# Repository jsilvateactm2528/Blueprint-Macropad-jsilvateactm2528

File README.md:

# Blueprint-Macropad-jsilvateactm2528
João Macropad is a 7 key macropad with 2 rotary encoders, an OLED Display. It also has 7 SK6812 MINI-E LEDs, and uses QMK firmware 

I spend a lot of hours on this build (I forgot to keep track of the time), because I'm new in this area and this is my first project. 

João Macropad is a compact macropad featuring 7 mechanical keys, 2 rotary encoders, a OLED display, and 7 rgb leds. 

It was designed as a personal open-source hardware project.

## Features

* 7 mechanical keys (For macros)
* 2 EC11 rotary encoder with push button (One change volume and mute and the other rotate to move up and down a list of options on the OLED screen and press to select one of the options.)
* 4 pin 128x32 OLED display (At the moment, I don´t know for sure what options I will have in the display.)
* 7 SK6812 MINI-E LEDs (Just to illuminate the macropad.)
* Seeed Studio XIAO microcontroller
* QMK firmware

## PCB

I used Kicad and it's a great program

* Shematics
* Pcb
* 3d view of the top and botom part of the pcb

## Case

The case was designed to be compact, simple, and functional, with easy access to all components from the top.

## Firmware

I used QMK for all of it

* One of the rotary encoder changes volume, press to mute and the other move up and down a list of options on the OLED screen and press to select one of the options.
* The 4 keys currently act as macros.
* The OLED will have a list of shortcuts (plan on ading the list via a windows app)
* The LEDs are normally changing between red, blue, green, and yellow.

## BOM

* 7x MX-Style switches
* 7x Keycaps
* 4x M3x5x4 Heatset inserts
* 4x M3x16mm screws
* 9x 1N4148 Diodes.
* 7x SK6812 MINI-E LEDs
* 1x 0.91" 128x32 OLED Display
* 2x EC11 Rotary Encoder
* 1x XIAO RP2040
* 1x Case (2 printed parts)
* 1x Custom pcb

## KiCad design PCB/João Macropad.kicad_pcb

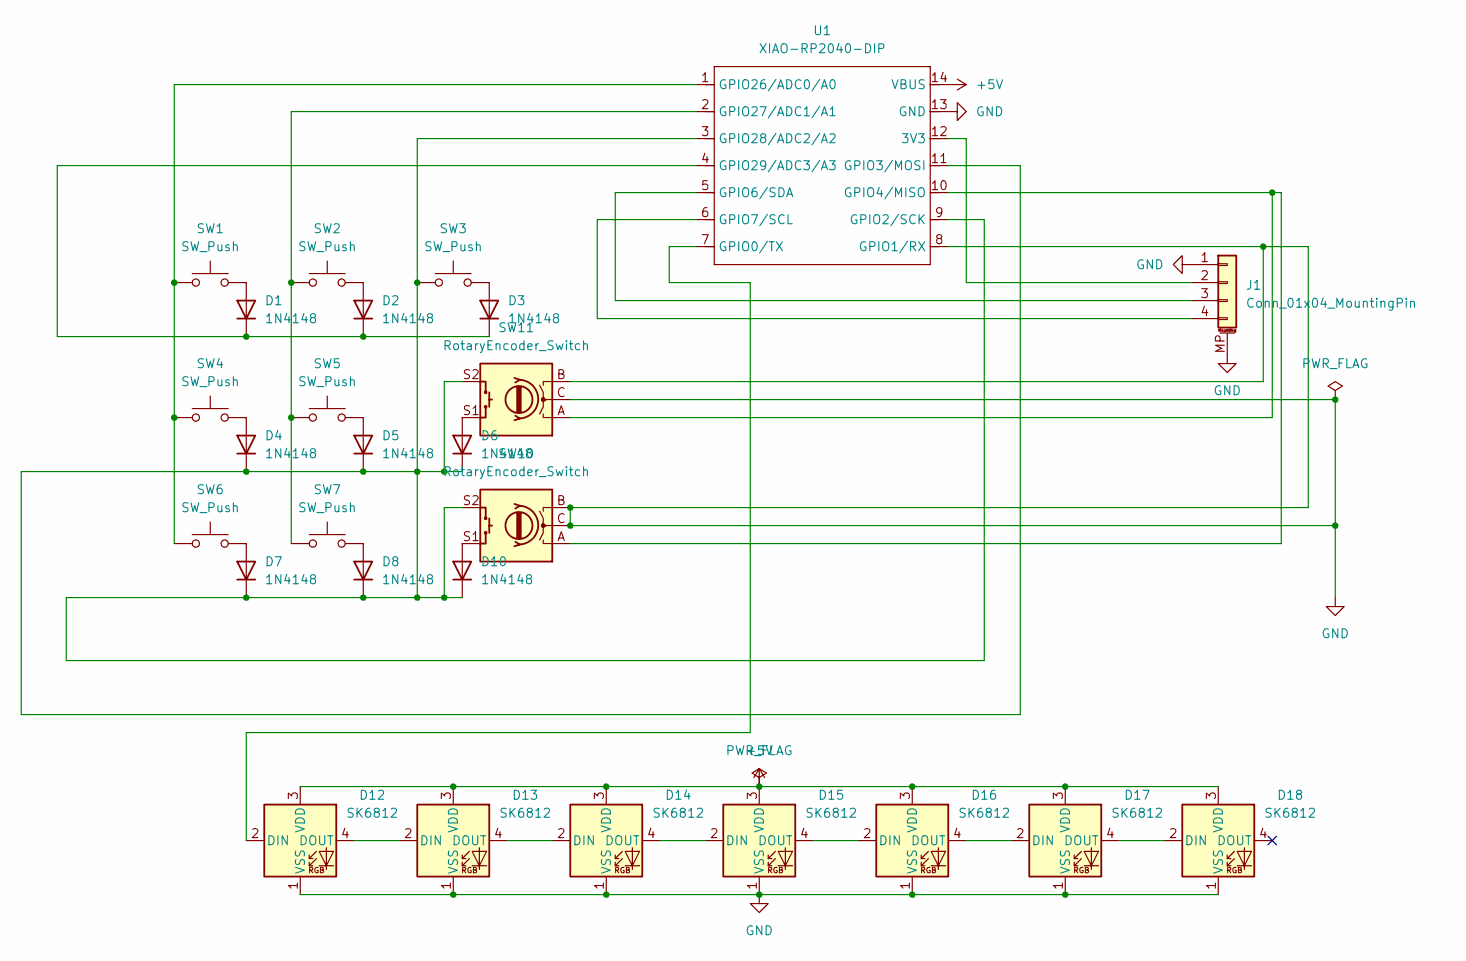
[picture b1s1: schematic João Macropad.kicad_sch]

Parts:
D1, D2, D3, D4, D5, D6, D7, D8, D10: 1N4148; D_DO-35_SOD27_P7.62mm_Horizontal
D12, D13, D14, D15, D16, D17, D18: SK6812; MX_SK6812MINI-E
J1: Conn_01x04_MountingPin; SSD1306-0.91-OLED-4pin-128x32 (2)
SW1, SW2, SW3, SW4, SW5, SW6, SW7: SW_Push; SW_Cherry_MX_1.00u_PCB
SW10, SW11: RotaryEncoder_Switch; RotaryEncoder_Alps_EC12E-Switch_Vertical_H20mm_CircularMoun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
U1: XIAO-RP2040-DIP

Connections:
+5V: D12.3 (VDD), D13.3 (VDD), D14.3 (VDD), D15.3 (VDD), D16.3 (VDD), D17.3 (VDD), D18.3 (VDD), U1.14 (VBUS)
GND: D12.1 (VSS), D13.1 (VSS), D14.1 (VSS), D15.1 (VSS), D16.1 (VSS), D17.1 (VSS), D18.1 (VSS), J1.1, J1.MP (MountPin), SW10.B, SW10.C, SW11.B, SW11.C, U1.8 (GPIO1/RX), U1.13 (GND)
unnamed: D1.2 (A), SW1.2
unnamed: D1.1 (K), D2.1 (K), D3.1 (K), U1.4 (GPIO29/ADC3/A3)
unnamed: D2.2 (A), SW2.2
unnamed: D3.2 (A), SW3.2
unnamed: D4.2 (A), SW4.2
unnamed: D5.2 (A), SW5.2
unnamed: D6.2 (A), SW11.S1
unnamed: D7.2 (A), SW6.2
unnamed: D8.2 (A), SW7.2
unnamed: D10.2 (A), SW10.S1
unnamed: D4.1 (K), D5.1 (K), D6.1 (K), D7.1 (K), D8.1 (K), D10.1 (K), SW3.1, SW10.S2, SW11.S2, U1.3 (GPIO28/ADC2/A2), U1.9 (GPIO2/SCK), U1.11 (GPIO3/MOSI)
unnamed: D12.2 (DIN), U1.7 (GPIO0/TX)
unnamed: D12.4 (DOUT), D13.2 (DIN)
unnamed: D13.4 (DOUT), D14.2 (DIN)
unnamed: D14.4 (DOUT), D15.2 (DIN)
unnamed: D15.4 (DOUT), D16.2 (DIN)
unnamed: D16.4 (DOUT), D17.2 (DIN)
unnamed: D17.4 (DOUT), D18.2 (DIN)
unnamed: J1.2, U1.12 (3V3)
unnamed: J1.3, U1.5 (GPIO6/SDA)
unnamed: J1.4, U1.6 (GPIO7/SCL)
unnamed: SW10.A, SW11.A, U1.10 (GPIO4/MISO)
unnamed: SW1.1, SW4.1, SW6.1, U1.1 (GPIO26/ADC0/A0)
unnamed: SW2.1, SW5.1, SW7.1, U1.2 (GPIO27/ADC1/A1)

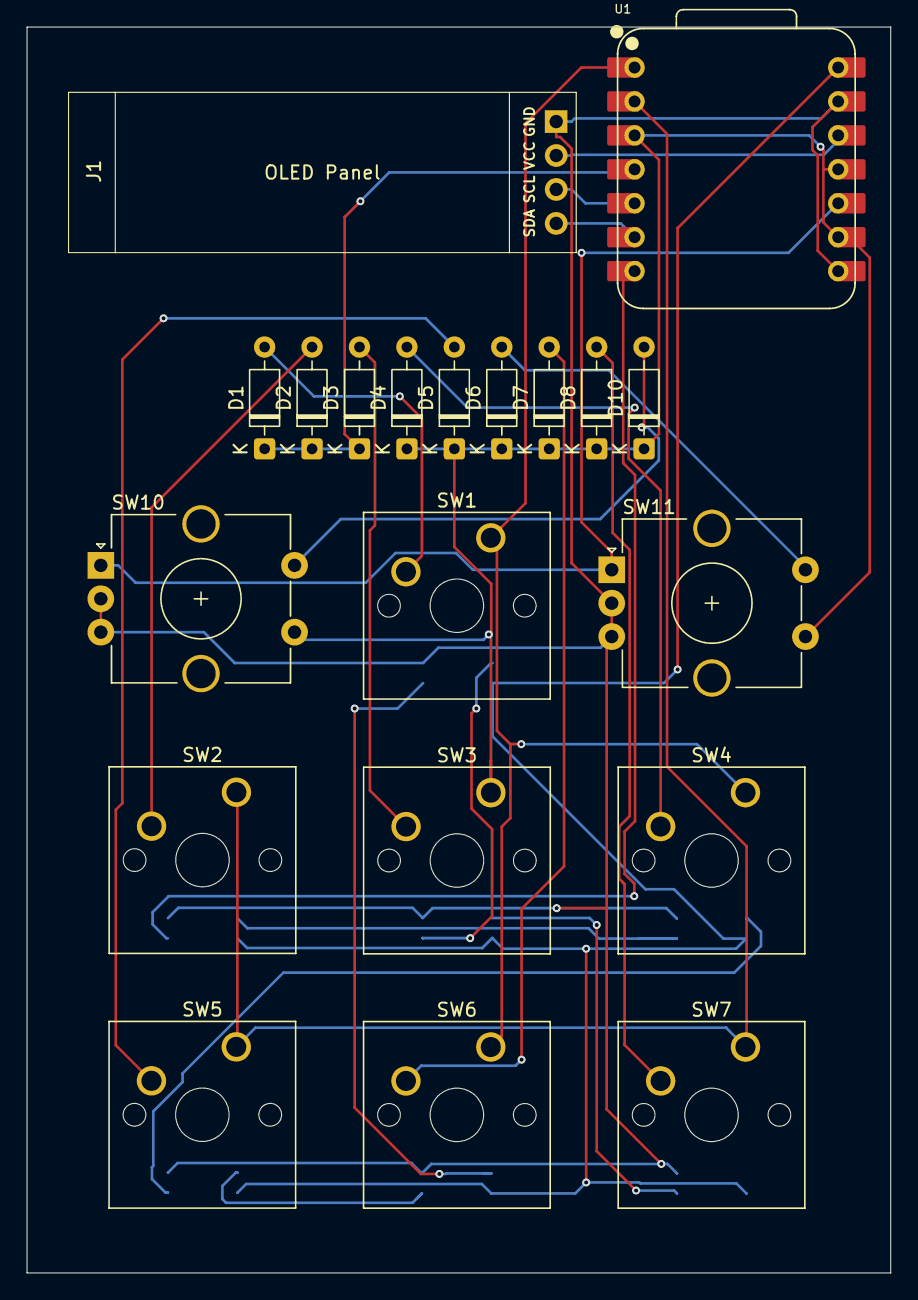
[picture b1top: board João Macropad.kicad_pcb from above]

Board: 2 copper layers, 64.6 x 93.2 mm, 27 parts (0 on the bottom side), 26 nets.
